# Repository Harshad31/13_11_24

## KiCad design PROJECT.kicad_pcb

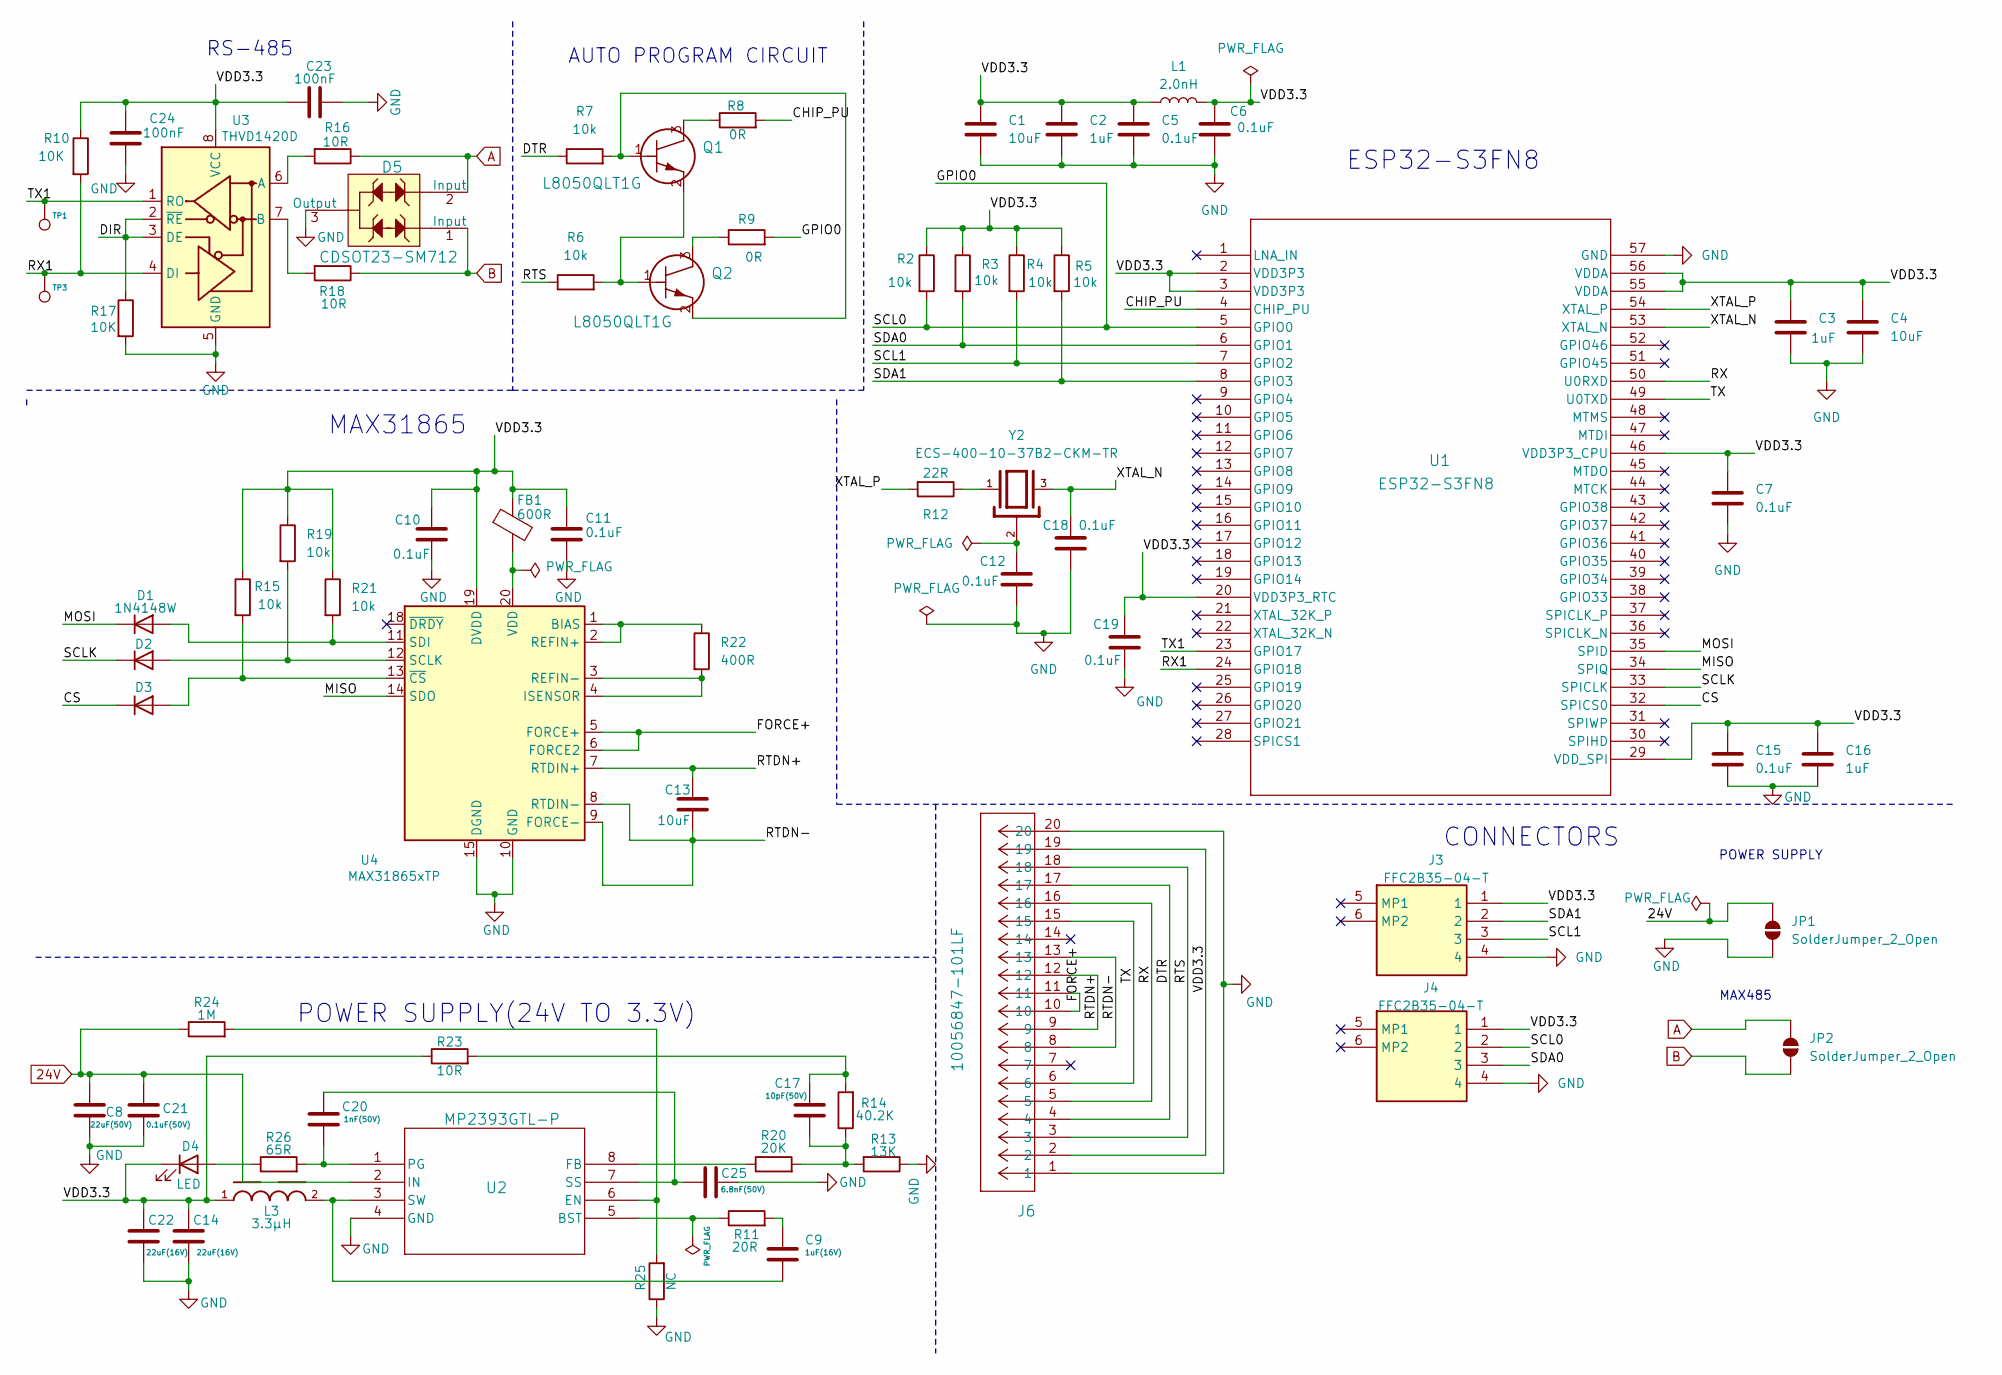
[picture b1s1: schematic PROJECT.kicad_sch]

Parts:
C1, C4, C13: 10uF; C_0201_0603Metric
C2, C3, C16: 1uF; C_0201_0603Metric
C5, C6, C7, C10, C11, C12, C15, C18, C19: 0.1uF; C_0201_0603Metric
C8: 22uF(50V); C_0805_2012Metric
C9: 1uF(16V); C_0201_0603Metric
C14, C22: 22uF(16V); C_0805_2012Metric
C17: 10pF(50V); C_0201_0603Metric
C20: 1nF(50V); C_0201_0603Metric
C21: 0.1uF(50V); C_0201_0603Metric
C23, C24: 100nF; C_0201_0603Metric
C25: 6.8nF(50V); C_0201_0603Metric
D1, D2, D3: 1N4148W; D_SOD-123F
D4: LED; LED_0201_0603Metric
D5: CDSOT23-SM712; SOT-23-3; MPN CDSOT23-SM712; Digi-Key_PN CDSOT23-SM712CT-ND
FB1: 600R; L_0603_1608Metric
J3, J4: FFC2B35-04-T; FFC2B3504T; Manufacturer_Part_Number FFC2B35-04-T
J6: 10056847-101LF; CONN_10056847-101LF_AMP
JP1, JP2: SolderJumper_2_Open; SolderJumper-2_P1.3mm_Open_Pad1.0x1.5mm
L1: 2.0nH; L_0201_0603Metric
L3: 3.3µH; WE-HCI_7050
Q1, Q2: L8050QLT1G; SC-59
R2, R3, R4, R5, R6, R7, R15, R19, R21: 10k; R_0201_0603Metric
R8, R9: 0R; R_0201_0603Metric
R10, R17: 10K; R_0201_0603Metric
R11: 20R; R_0201_0603Metric
R12: 22R; R_0201_0603Metric
R13: 13K; R_0201_0603Metric
R14: 40.2K; R_0201_0603Metric
R16, R18, R23: 10R; R_0201_0603Metric
R20: 20K; R_0201_0603Metric
R22: 400R; R_0201_0603Metric
R24: 1M; R_0201_0603Metric
R25: NC; R_0201_0603Metric
R26: 65R; R_0201_0603Metric
TP1, TP3: TestPoint; TestPoint_Pad_D1.0mm
U1: ESP32-S3FN8; ESP32 S3FN8_7X7_EXP-
U2: MP2393GTL-P; SOT583_MP2393
U3: THVD1420D; SOIC-8_3.9x4.9mm_P1.27mm
U4: MAX31865xTP; TQFN-20-1EP_5x5mm_P0.65mm_EP3.25x3.25mm
Y2: ECS-400-10-37B2-CKM-TR; XTAL_ECS-400-10-37B2-CKM-TR; PARTREV 2021

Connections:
24V: C8.1, C21.1, JP1.2 (B), R24.1, U2.2 (IN)
/CHIP_PU: R8.2, U1.4 (CHIP_PU)
/CS: D3.1 (K), U1.32 (SPICS0)
/DIR: R17.1, U3.2 (~RE), U3.3 (DE)
/DTR: J6.4, J6.17, R7.1
/FORCE+: J6.10, J6.11, U4.5 (FORCE+), U4.6 (FORCE2)
/GPIO0: J4.2, R2.2, R9.2, U1.5 (GPIO0)
/MISO: U1.34 (SPIQ), U4.14 (SDO)
/MOSI: D1.1 (K), U1.35 (SPID)
/RTDN+: C13.1, J6.9, J6.12, U4.7 (RTDIN+)
/RTDN-: C13.2, J6.8, J6.13, U4.8 (RTDIN-), U4.9 (FORCE-)
/RTS: J6.3, J6.18, R6.1
/RX: J6.5, J6.16, U1.50 (U0RXD)
/RX1: R10.2, TP3.1, U1.24 (GPIO18), U3.4 (DI)
/SCL1: J3.3, R4.2, U1.7 (GPIO2)
/SCLK: D2.1 (K), U1.33 (SPICLK)
/SDA0: J4.3, R3.2, U1.6 (GPIO1)
/SDA1: J3.2, R5.2, U1.8 (GPIO3)
/TX: J6.6, J6.15, U1.49 (U0TXD)
/TX1: TP1.1, U1.23 (GPIO17), U3.1 (RO)
/VDD3.3: C1.1, C2.1, C3.1, C4.1, C5.1, C6.1, C7.1, C10.1, C11.1, C14.1, C15.1, C16.1, C19.1, C22.1, C23.1, C24.2, D4.1 (K), FB1.1, J3.1, J4.1, J6.2, J6.19, L1.1, L1.2, L3.1, R2.1, R3.1, R4.1, R5.1, R10.1, R15.1, R19.1, R21.1, R23.1, U1.2 (VDD3P3), U1.3 (VDD3P3), U1.20 (VDD3P3_RTC), U1.29 (VDD_SPI), U1.46 (VDD3P3_CPU), U1.55 (VDDA), U1.56 (VDDA), U3.8 (VCC), U4.19 (DVDD)
/XTAL_N: C18.1, U1.53 (XTAL_N), Y2.3
/XTAL_P: R12.2, U1.54 (XTAL_P)
A: D5.2 (Input), JP2.2 (B), R16.1
B: D5.1 (Input), JP2.1 (A), R18.1
GND: C1.2, C2.2, C3.2, C4.2, C5.2, C6.2, C7.2, C8.2, C10.2, C11.2, C12.2, C14.2, C15.2, C16.2, C18.2, C19.2, C21.2, C22.2, C23.2, C24.1, C25.2, D5.3 (Output), J3.4, J4.4, J6.1, J6.20, JP1.1 (A), R13.1, R17.2, R25.1, U1.57 (GND), U2.4 (GND), U3.5 (GND), U4.10 (GND), U4.15 (DGND), U4.16 (GND), U4.21 (GND)
unnamed: C9.1, R11.2
unnamed: C12.1, Y2.2
unnamed: C17.1, R13.2, R14.1, R20.2
unnamed: C17.2, R14.2, R23.2
unnamed: D1.2 (A), R21.2, U4.11 (SDI)
unnamed: D2.2 (A), R19.2, U4.12 (SCLK)
unnamed: D3.2 (A), R15.2, U4.13 (~CS)
unnamed: D4.2 (A), R26.1
unnamed: Q1.1, Q2.2, R7.2
unnamed: Q1.2, Q2.1, R6.2
unnamed: Q1.3, R8.1
unnamed: Q2.3, R9.1
unnamed: R12.1, Y2.1
unnamed: R11.1, U2.5 (BST)
unnamed: R24.2, R25.2, U2.6 (EN)
unnamed: R20.1, U2.8 (FB)
unnamed: C20.2, R26.2, U2.1 (PG)
unnamed: C20.1, C25.1, U2.7 (SS)
unnamed: C9.2, L3.2, U2.3 (SW)
unnamed: R16.2, U3.6 (A)
unnamed: R18.2, U3.7 (B)
unnamed: R22.1, U4.1 (BIAS), U4.2 (REFIN+)
unnamed: R22.2, U4.3 (REFIN-), U4.4 (ISENSOR)
unnamed: FB1.2, U4.20 (VDD)

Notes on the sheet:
POWER SUPPLY
MAX31865
ESP32-S3FN8
RS-485
AUTO PROGRAM CIRCUIT
CONNECTORS
POWER SUPPLY(24V TO 3.3V)
MAX485

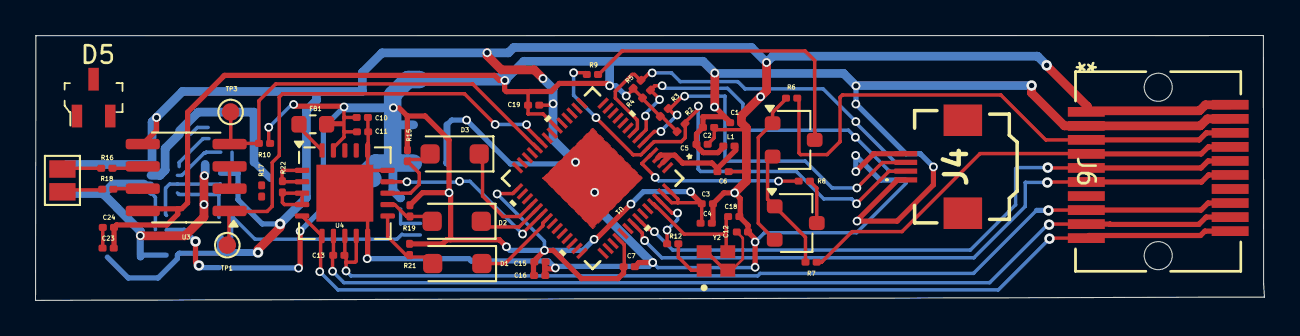
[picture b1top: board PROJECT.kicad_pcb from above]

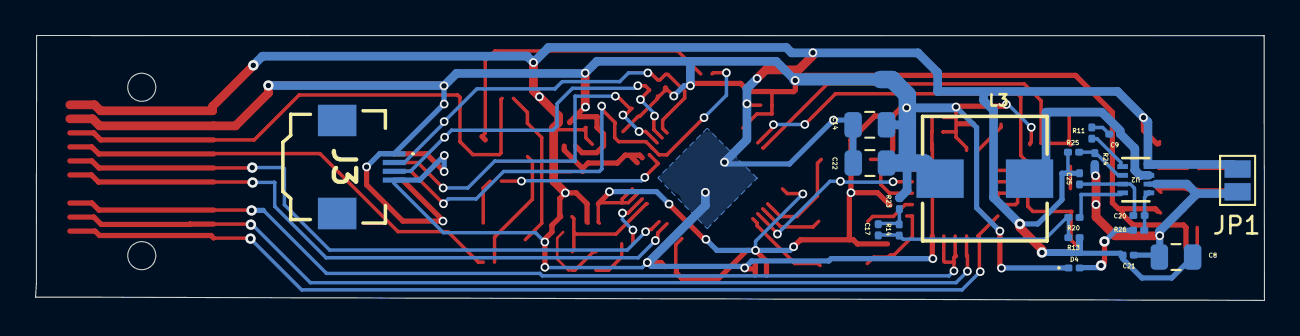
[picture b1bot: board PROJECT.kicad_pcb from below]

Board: 2 copper layers, 70.1 x 15.1 mm, 72 parts (21 on the bottom side), 50 nets.
